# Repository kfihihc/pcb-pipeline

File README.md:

# pcb-pipeline: skills, toolkit and merge gate for open-source PCB design

English | [中文](README.zh-CN.md)

A set of skills for Claude Code and Codex (Agent Skills format) plus pcbkit, a toolkit that is copied into each board project at a fixed version. Together they cover the whole KiCad 10 board flow:

requirements → parts → datasheet facts → official reference design comparison → schematic as code → simulation → rules, placement, routing → gate → review → release

```mermaid
flowchart LR
  classDef agent stroke:#3987e5,stroke-width:2px
  classDef human stroke:#d95926,stroke-width:2px
  classDef tool stroke:#199e70,stroke-width:2px
  S1(Requirements):::agent --> S2(Parts):::agent --> S3(Datasheets):::agent --> S4(Reference design):::agent --> S5(Schematic):::agent --> S6(Simulation):::agent --> S7(Layout):::agent
  S7 --> G{8-check gate}:::tool
  G -- fail --> S7
  G -- pass --> R{{Review}}:::human --> P(Release):::agent --> B{{Bring-up}}:::human
  B -- errata --> S1
```

The principles:

- KiCad is the single source of truth for the board.
- Design intent is kept as text.
- Every change passes a deterministic gate in Git and CI.
- Routing uses open routers.
- Agents change a design only through branches, change notes and pull requests.

> **Language.** The skill instructions and the project documents are written in Chinese. Every skill description includes an English sentence to help agents identify relevant tasks in English; automatic selection has not been systematically evaluated.

- How to use it: [docs/SKILLS.zh-CN.md](docs/SKILLS.zh-CN.md) (Chinese). It has an overview diagram, a quick reference for the ten skills, example prompts, the life cycle of one change, the evidence chain and the data flow.
- Why it is designed this way and what was verified: [PIPELINE.zh-CN.md](PIPELINE.zh-CN.md) (Chinese).
- The diagrams are Mermaid, which GitHub renders directly. For other viewers, SVG copies are in `docs/diagrams/`.

It grew out of an earlier survey of AI and EDA tools for hardware design (not part of this repository) and the experience of building a KiCad replica of an ESP32-S3 AMOLED board.

## Skills

| Skill | What it does | Bundled scripts |
| --- | --- | --- |
| `pcb-pipeline` | Orchestrator: stages, artifacts, rules for transactional changes; creates or adopts a project; upgrades pcbkit | `scripts/new_project.py`, `kit/`, `assets/template/` |
| `pcb-parts` | Offline search of the JLCPCB/LCSC parts library, alternates, BOM stock and cost, live prices | `scripts/jlc_parts.py` |
| `pcb-datasheet` | Datasheet download with provenance, per-page search and rendering, `facts.toml` with page references, pinout check against KiCad | `scripts/datasheet.py` |
| `pcb-refdesign` | Export of official reference designs (KiCad, Altium, EAGLE, PDF), chip-centred surroundings, pin-by-pin comparison | `scripts/refnet.py` |
| `pcb-schematic` | SKiDL circuit code → readable KiCad schematic; connectivity intent | (in the project: `pcbkit/sch_gen.py`) |
| `pcb-sim` | SPICE benches, corners and assertions (libngspice) | (in the project: `pcbkit/sim.py`) |
| `pcb-layout` | Board outline, rules, net classes, pours, keepouts; sync, placement, pre-routing; transactional routing with KiCadRoutingTools | `scripts/setup_krt.sh` |
| `pcb-gate` | The 8-check gate, declarative metrics, CI, revision diff and change-scope check | (in the project: `pcbkit/gate.py`, `metrics.py`, `board_diff.py`) |
| `pcb-review` | Review packet (KiCanvas, interactive BOM, PcbDraw drawings, EMC pre-check leads), reviewer plus devil's-advocate passes, findings turned into gate checks | `scripts/setup_kicad_happy.sh` (in the project: `pcbkit/review.py`) |
| `pcb-release` | Fabrication and review package, JLCPCB BOM/CPL, interactive BOM, panelization (the user decides), pre-order checks, tagging | (in the project: `pcbkit/release.py`, `extras.py`) |

The gate runs these 8 checks:

1. ERC.
2. DRC with schematic parity.
3. A rules canary: a broken `.kicad_dru` is otherwise dropped silently.
4. Zone refill.
5. Netlist checks: connectivity intent, pins against pads, BOM fields and the parts register.
6. Board metrics.
7. Simulation assertions.
8. Reproduction of generated files.

## Installing the skills

### 1. Prerequisites

| Needed for | Requirement |
| --- | --- |
| Everything | Linux with KiCad 10 from your distribution: `kicad-cli` and KiCad's `pcbnew` Python module. Tested with Debian's KiCad 10.0.6 and Python 3.14. pcbkit uses the system KiCad and never downloads its own copy |
| Datasheets | poppler-utils (`pdftotext`, `pdfinfo`, `pdftoppm`) |
| Simulation | libngspice (Debian: `libngspice0`, already pulled in by KiCad) |
| Board projects | [uv](https://docs.astral.sh/uv/) for the Python dependency groups (SKiDL, router, optional outputs), and git |
| Tests only | rsync |
| The agent | [Claude Code](https://claude.com/claude-code) and/or Codex |

On Debian or Ubuntu:

```bash
sudo apt install kicad poppler-utils libngspice0 git rsync pipx
pipx install uv          # or the installer from the uv website
```

### 2. Get the repository

```bash
git clone https://github.com/kfihihc/pcb-pipeline.git
cd pcb-pipeline
```

Keep the clone: the skills are installed as symbolic links into it.

### 3. Link the skills

`install.sh` links every folder under `skills/` into the personal skill folders of Claude Code (`~/.claude/skills/`) and Codex (`~/.codex/skills/`). It links only into folders that already exist, so create the ones for the agents you use first:

```bash
mkdir -p ~/.claude/skills     # Claude Code
mkdir -p ~/.codex/skills      # Codex, only if you use it
./install.sh
```

Expected output, once per skill and agent:

```
linked  /home/you/.claude/skills/pcb-pipeline
linked  /home/you/.claude/skills/pcb-parts
...
```

- `skip … (not present)` means that agent's skill folder does not exist; create it and run `./install.sh` again.
- `CONFLICT … exists and is not a link` means a skill of the same name is already installed. The script leaves it untouched; move it away first if you want this one.

Install all ten skills. They refer to each other: the orchestrator hands work to the stage skills, and the release skill uses references from the layout skill.

### 4. Check the installation

```bash
./install.sh --check
```

This lists every link (`ok`, `missing` or `CONFLICT`) and checks the dependencies: `kicad-cli`, poppler, uv, git, libngspice, the parts database, the router and kicad-happy.

Then start a **new** Claude Code session so it loads the skills, and try one of these:

- type `/pcb-pipeline`;
- or just describe the task, for example "Design a small USB-C to 3.3 V board with pcb-pipeline". The agent chooses the skill from its description.

The ten skills have been discovered in both Claude Code and Codex, and their instructions have been read in Codex. This verifies discovery and access, not an end-to-end board design run in both agents.

### 5. One-time downloads (when a stage first needs them)

All of these go to `~/.cache/pcb-pipeline/`, outside the repository:

| For | Command | Notes |
| --- | --- | --- |
| Parts search (`pcb-parts`) | `python3 skills/pcb-parts/scripts/jlc_parts.py fetch --db current` | JLCPCB parts database, about 180 MB |
| Autorouting (`pcb-layout`) | `skills/pcb-layout/scripts/setup_krt.sh` | KiCadRoutingTools v0.22.1 with its own uv environment |
| EMC pre-check (`pcb-review`, optional) | `skills/pcb-review/scripts/setup_kicad_happy.sh` | kicad-happy v2.3.1; only its analysis scripts are used, its skills are not installed |

The optional outputs (KiKit panel, InteractiveHtmlBom, PcbDraw) are installed per board project, in that project's uv environment: run `uv sync --group extras` in the project. `kicanvas.js` ships with pcbkit. [docs/external-tools.zh-CN.md](docs/external-tools.zh-CN.md) (Chinese) explains how these tools were chosen and why KiBot is not used.

### Updating and removing

- **Update the skills:** `git pull` in the clone. The links pick up the change at once; start a new agent session.
- **Update a board project's toolkit:** each project keeps its own copy of pcbkit, so upgrade it deliberately, on its own branch, then run the gate:

  ```bash
  python3 <clone>/skills/pcb-pipeline/scripts/new_project.py <board> --update-kit
  ```
- **Remove:** `./install.sh --uninstall` removes only the links that point into this clone.

### Other ways to install

- **One project only (Claude Code):** link the skill folders into that project's `.claude/skills/` instead of `~/.claude/skills/`.
- **Copy instead of link:** copying `skills/*` also works, but then `git pull` no longer updates them.

## Quick start

```bash
P=$PWD/skills       # run inside the pcb-pipeline clone
python3 "$P/pcb-pipeline/scripts/new_project.py" ~/boards/my-board --name my-board --title "My board" --size 40x30
cd ~/boards/my-board && git init
# then tell Claude Code / Codex: "Design this board with pcb-pipeline. The requirements are ..."
python3 pcbkit/gate.py          # the gate; run it at any time
```

To adopt an existing KiCad project:

```bash
# Run from the pcb-pipeline clone; replace /path/to/existing-board.
python3 skills/pcb-pipeline/scripts/new_project.py /path/to/existing-board \
  --adopt --pcb x.kicad_pcb --sch x.kicad_sch
```

See `examples/s3-adoption/` for a worked case.

## Examples

- [examples/usb-ldo/](examples/usb-ldo/): a small two-layer board taken from nothing to a fabrication package. Its README lists the problems each stage actually caught.
- [examples/s3-adoption/](examples/s3-adoption/): the gate applied to the S3 AMOLED replica, with its 30 existing thresholds rewritten as declarative metrics.

## Tests

```bash
tests/run_tests.sh        # about 2 minutes
```

The suite runs the example's gate and negative tests for each check. It also covers simulation, reference designs, parts search, datasheets, and the optional outputs including panelization. A test whose data or tool is missing is skipped, not failed.

## License

MIT, see [LICENSE](LICENSE). This covers the skills, pcbkit, the documentation and the example designs.

New board projects default to MIT; use `new_project.py --license <identifier>` to choose another license. Check the upstream license when adopting or deriving an existing design.

Exceptions:

- **KiCanvas:** `kicanvas.js` (`skills/pcb-pipeline/kit/vendor/` and its copy in the example) keeps its own MIT license and copyright, in `kicanvas.LICENSE.md` next to it.
- **KiCad libraries:** symbols and footprints from the KiCad libraries used in the example boards are under the KiCad library license (CC-BY-SA 4.0 with an exception for designs that use them).
- **Tools fetched at setup:** these keep their own licenses. All are MIT: KiCadRoutingTools, kicad-happy, KiKit, InteractiveHtmlBom and PcbDraw.

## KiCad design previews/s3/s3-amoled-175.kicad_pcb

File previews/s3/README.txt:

Open in a browser over HTTP (file:// does not work):
  python3 -m http.server --directory s3 8000
  then http://localhost:8000/   (any free port; Ctrl+C stops the server)

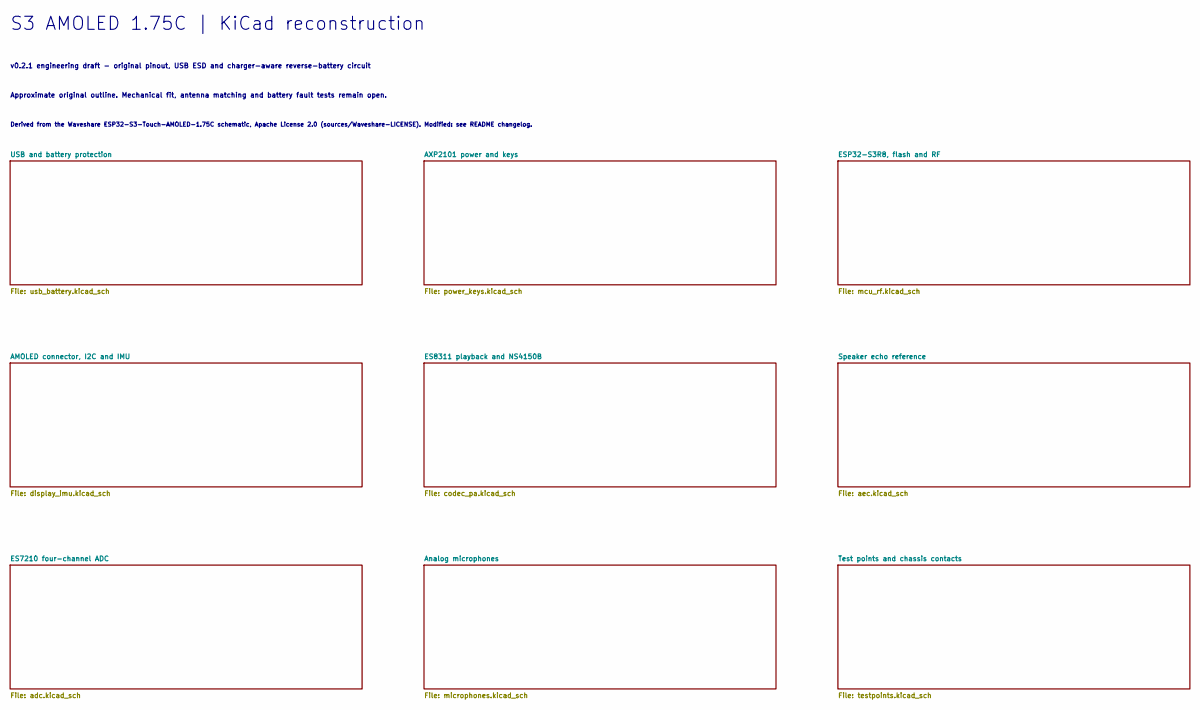
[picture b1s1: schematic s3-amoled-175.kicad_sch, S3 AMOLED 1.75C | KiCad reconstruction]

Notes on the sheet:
Approximate original outline. Mechanical fit, antenna matching and battery fault tests remain open.
v0.2.1 engineering draft - original pinout, USB ESD and charger-aware reverse-battery circuit
S3 AMOLED 1.75C | KiCad reconstruction
Derived from the Waveshare ESP32-S3-Touch-AMOLED-1.75C schematic, Apache License 2.0 (sources/Waveshare-LICENSE). Modified: see README changelog.

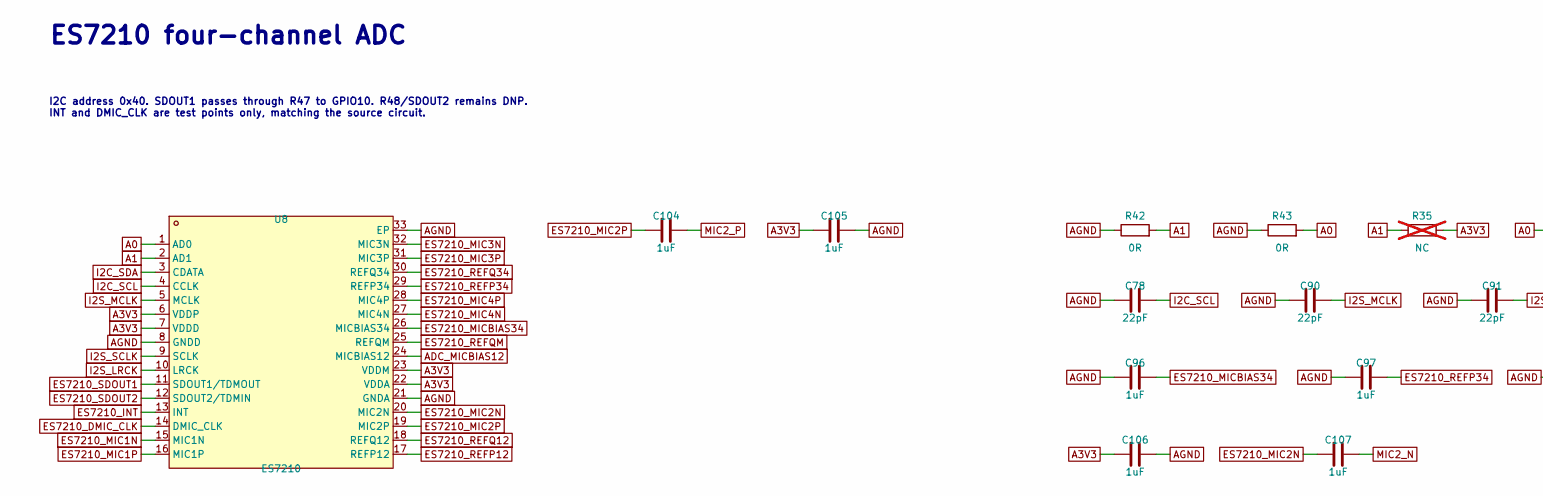
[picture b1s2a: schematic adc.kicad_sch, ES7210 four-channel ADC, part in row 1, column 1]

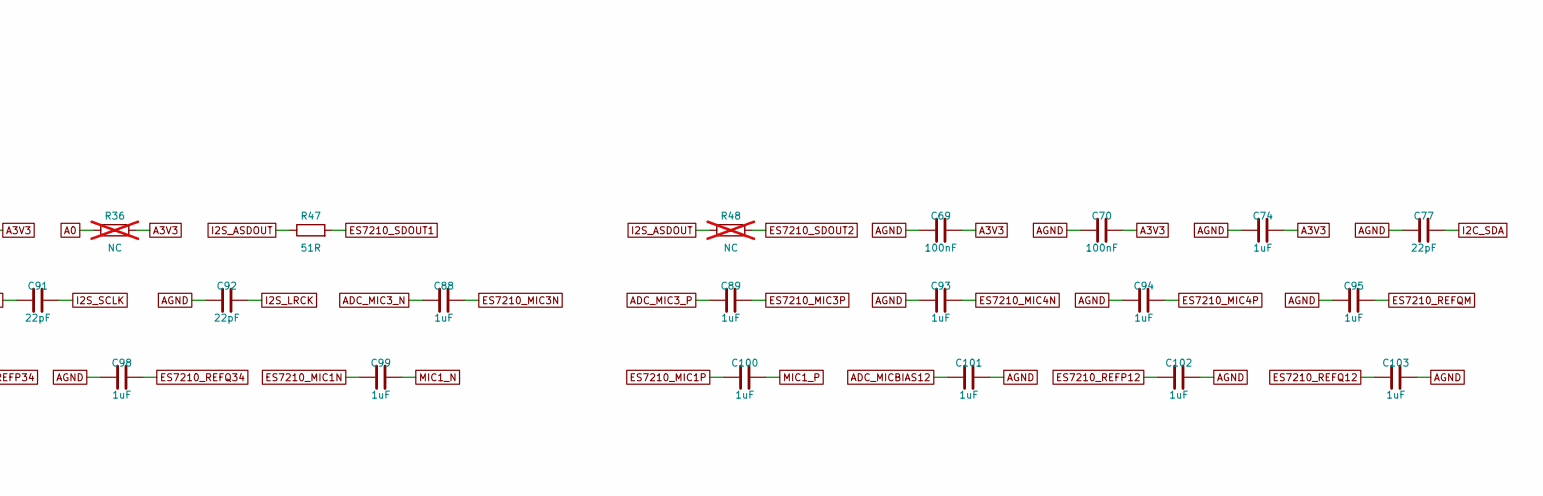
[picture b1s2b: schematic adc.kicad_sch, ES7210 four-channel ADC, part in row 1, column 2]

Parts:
C69, C70: 100nF; C_0201_0603Metric_Tight; LCSC C190183
C74, C88, C89, C93, C94, C95, C96, C97, C98, C99, C100, C101, C102, C103, C104, C105, C106, C107: 1uF; C_0201_0603Metric_Tight; LCSC C76929
C77, C78, C90, C91, C92: 22pF; C_0201_0603Metric_Tight; LCSC C272881
R35, R36: NC; R_0402_1005Metric_Tight; not fitted
R42, R43: 0R; R_0402_1005Metric_Tight; LCSC C17168
R47: 51R; R_0201_0603Metric_Tight; LCSC C163499
R48: NC; R_0201_0603Metric_Tight; not fitted
U8: ES7210; QFN-32_L4.0-W4.0-P0.40-BL-EP2.7; MPN ES7210; LCSC C365743

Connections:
A0: R36.1, R43.2, U8.1 (AD0)
A1: R35.1, R42.2, U8.2 (AD1)
A3V3: C69.2, C70.2, C74.2, C105.1, C106.1, R35.2, R36.2, U8.6 (VDDP), U8.7 (VDDD), U8.22 (VDDA), U8.23 (VDDM); also elsewhere on the board
ADC_MIC3_N: C88.1; also elsewhere on the board
ADC_MIC3_P: C89.1; also elsewhere on the board
ADC_MICBIAS12: C101.1, U8.24 (MICBIAS12); also elsewhere on the board
AGND: C69.1, C70.1, C74.1, C77.1, C78.1, C90.1, C91.1, C92.1, C93.1, C94.1, C95.1, C96.1, C97.1, C98.1, C101.2, C102.2, C103.2, C105.2, C106.2, R42.1, R43.1, U8.8 (GNDD), U8.21 (GNDA), U8.33 (EP); also elsewhere on the board
ES7210_DMIC_CLK: U8.14 (DMIC_CLK); also elsewhere on the board
ES7210_INT: U8.13 (INT); also elsewhere on the board
ES7210_MIC1N: C99.1, U8.15 (MIC1N)
ES7210_MIC1P: C100.1, U8.16 (MIC1P)
ES7210_MIC2N: C107.1, U8.20 (MIC2N)
ES7210_MIC2P: C104.1, U8.19 (MIC2P)
ES7210_MIC3N: C88.2, U8.32 (MIC3N)
ES7210_MIC3P: C89.2, U8.31 (MIC3P)
ES7210_MIC4N: C93.2, U8.27 (MIC4N)
ES7210_MIC4P: C94.2, U8.28 (MIC4P)
ES7210_MICBIAS34: C96.2, U8.26 (MICBIAS34)
ES7210_REFP12: C102.1, U8.17 (REFP12)
ES7210_REFP34: C97.2, U8.29 (REFP34)
ES7210_REFQ12: C103.1, U8.18 (REFQ12)
ES7210_REFQ34: C98.2, U8.30 (REFQ34)
ES7210_REFQM: C95.2, U8.25 (REFQM)
ES7210_SDOUT1: R47.2, U8.11 (SDOUT1/TDMOUT)
ES7210_SDOUT2: R48.2, U8.12 (SDOUT2/TDMIN)
I2C_SCL: C78.2, U8.4 (CCLK); also elsewhere on the board
I2C_SDA: C77.2, U8.3 (CDATA); also elsewhere on the board
I2S_ASDOUT: R47.1, R48.1; also elsewhere on the board
I2S_LRCK: C92.2, U8.10 (LRCK); also elsewhere on the board
I2S_MCLK: C90.2, U8.5 (MCLK); also elsewhere on the board
I2S_SCLK: C91.2, U8.9 (SCLK); also elsewhere on the board
MIC1_N: C99.2; also elsewhere on the board
MIC1_P: C100.2; also elsewhere on the board
MIC2_N: C107.2; also elsewhere on the board
MIC2_P: C104.2; also elsewhere on the board

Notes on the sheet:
ES7210 four-channel ADC
I2C address 0x40. SDOUT1 passes through R47 to GPIO10. R48/SDOUT2 remains DNP. INT and DMIC_CLK are test points only, matching the source circuit.

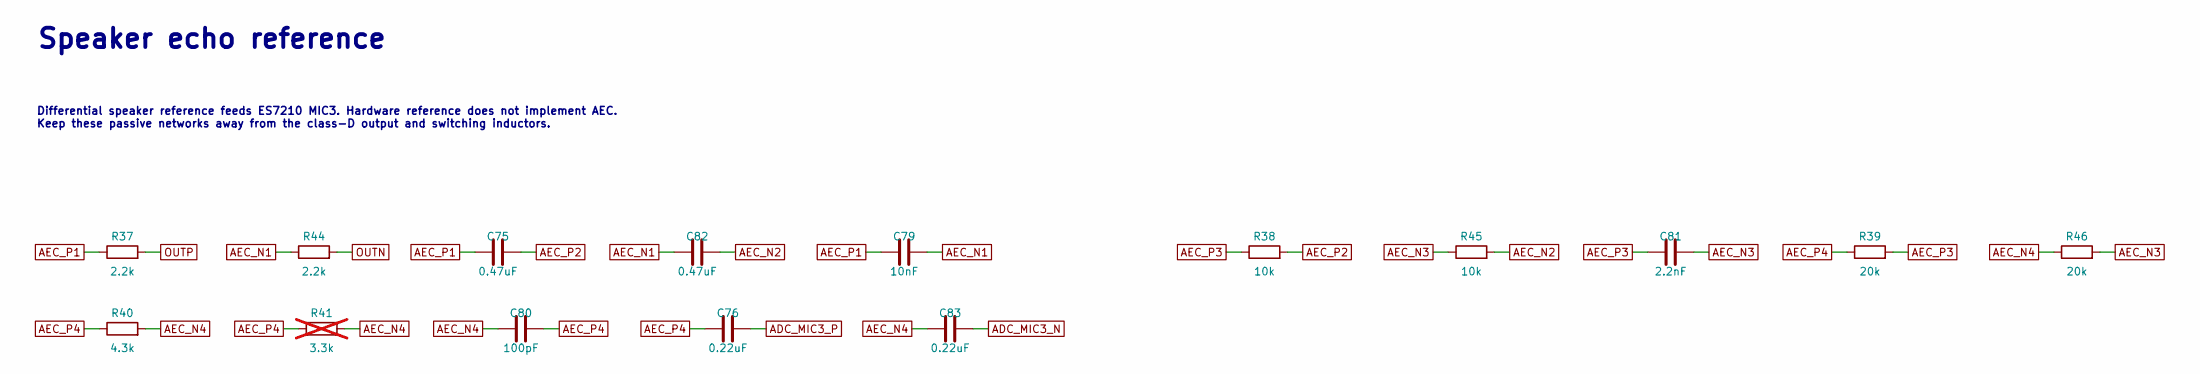
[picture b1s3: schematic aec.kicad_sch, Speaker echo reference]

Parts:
C75, C82: 0.47uF; C_0201_0603Metric_Tight; LCSC C88915
C76, C83: 0.22uF; C_0201_0603Metric_Tight; LCSC C76932
C79: 10nF; C_0201_0603Metric_Tight; LCSC C285010
C80: 100pF; C_0201_0603Metric_Tight; LCSC C272870
C81: 2.2nF; C_0201_0603Metric_Tight; LCSC C80433
R37, R44: 2.2k; R_0201_0603Metric_Tight; LCSC C142018
R38, R45: 10k; R_0201_0603Metric_Tight; LCSC C473048
R39, R46: 20k; R_0201_0603Metric_Tight; LCSC C295787
R40: 4.3k; R_0201_0603Metric_Tight; LCSC C423525
R41: 3.3k; R_0201_0603Metric_Tight; not fitted

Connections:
ADC_MIC3_N: C83.2; also elsewhere on the board
ADC_MIC3_P: C76.2; also elsewhere on the board
AEC_N1: C79.2, C82.1, R44.1
AEC_N2: C82.2, R45.2
AEC_N3: C81.2, R45.1, R46.2
AEC_N4: C80.1, C83.1, R40.2, R41.2, R46.1
AEC_P1: C75.1, C79.1, R37.1
AEC_P2: C75.2, R38.2
AEC_P3: C81.1, R38.1, R39.2
AEC_P4: C76.1, C80.2, R39.1, R40.1, R41.1
OUTN: R44.2; also elsewhere on the board
OUTP: R37.2; also elsewhere on the board

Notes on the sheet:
Speaker echo reference
Differential speaker reference feeds ES7210 MIC3. Hardware reference does not implement AEC. Keep these passive networks away from the class-D output and switching inductors.

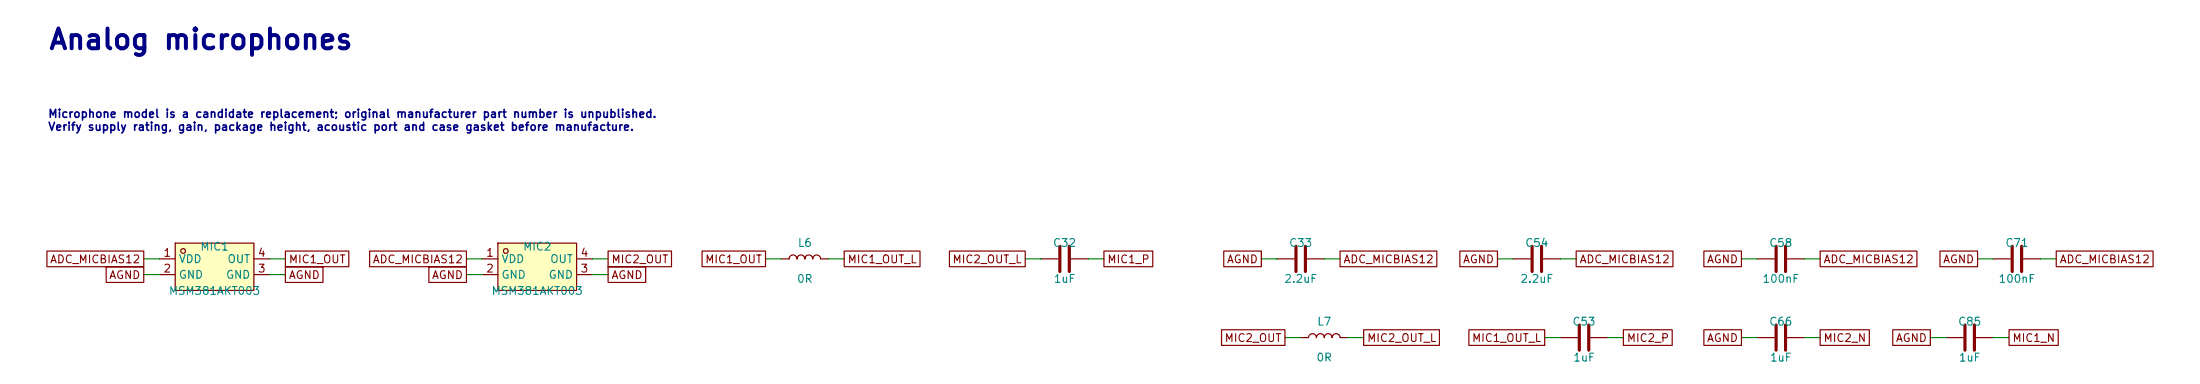
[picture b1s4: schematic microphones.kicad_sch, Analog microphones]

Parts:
C32, C53, C66, C85: 1uF; C_0201_0603Metric_Tight; LCSC C76929
C33, C54: 2.2uF; C_0201_0603Metric_Tight; LCSC C386031
C58, C71: 100nF; C_0201_0603Metric_Tight; LCSC C190183
L6, L7: 0R; R_0201_0603Metric_Tight; LCSC C106227
MIC1, MIC2: MSM381AKT003; MIC_MSM381AKT003_Tight; MPN MSM381AKT003; LCSC C51928211

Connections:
ADC_MICBIAS12: C33.2, C54.2, C58.2, C71.2, MIC1.1 (VDD), MIC2.1 (VDD); also elsewhere on the board
AGND: C33.1, C54.1, C58.1, C66.1, C71.1, C85.1, MIC1.2 (GND), MIC1.3 (GND), MIC2.2 (GND), MIC2.3 (GND); also elsewhere on the board
MIC1_N: C85.2; also elsewhere on the board
MIC1_OUT: L6.1, MIC1.4 (OUT)
MIC1_OUT_L: C53.1, L6.2
MIC1_P: C32.2; also elsewhere on the board
MIC2_N: C66.2; also elsewhere on the board
MIC2_OUT: L7.1, MIC2.4 (OUT)
MIC2_OUT_L: C32.1, L7.2
MIC2_P: C53.2; also elsewhere on the board

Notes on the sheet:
Microphone model is a candidate replacement; original manufacturer part number is unpublished. Verify supply rating, gain, package height, acoustic port and case gasket before manufacture.
Analog microphones

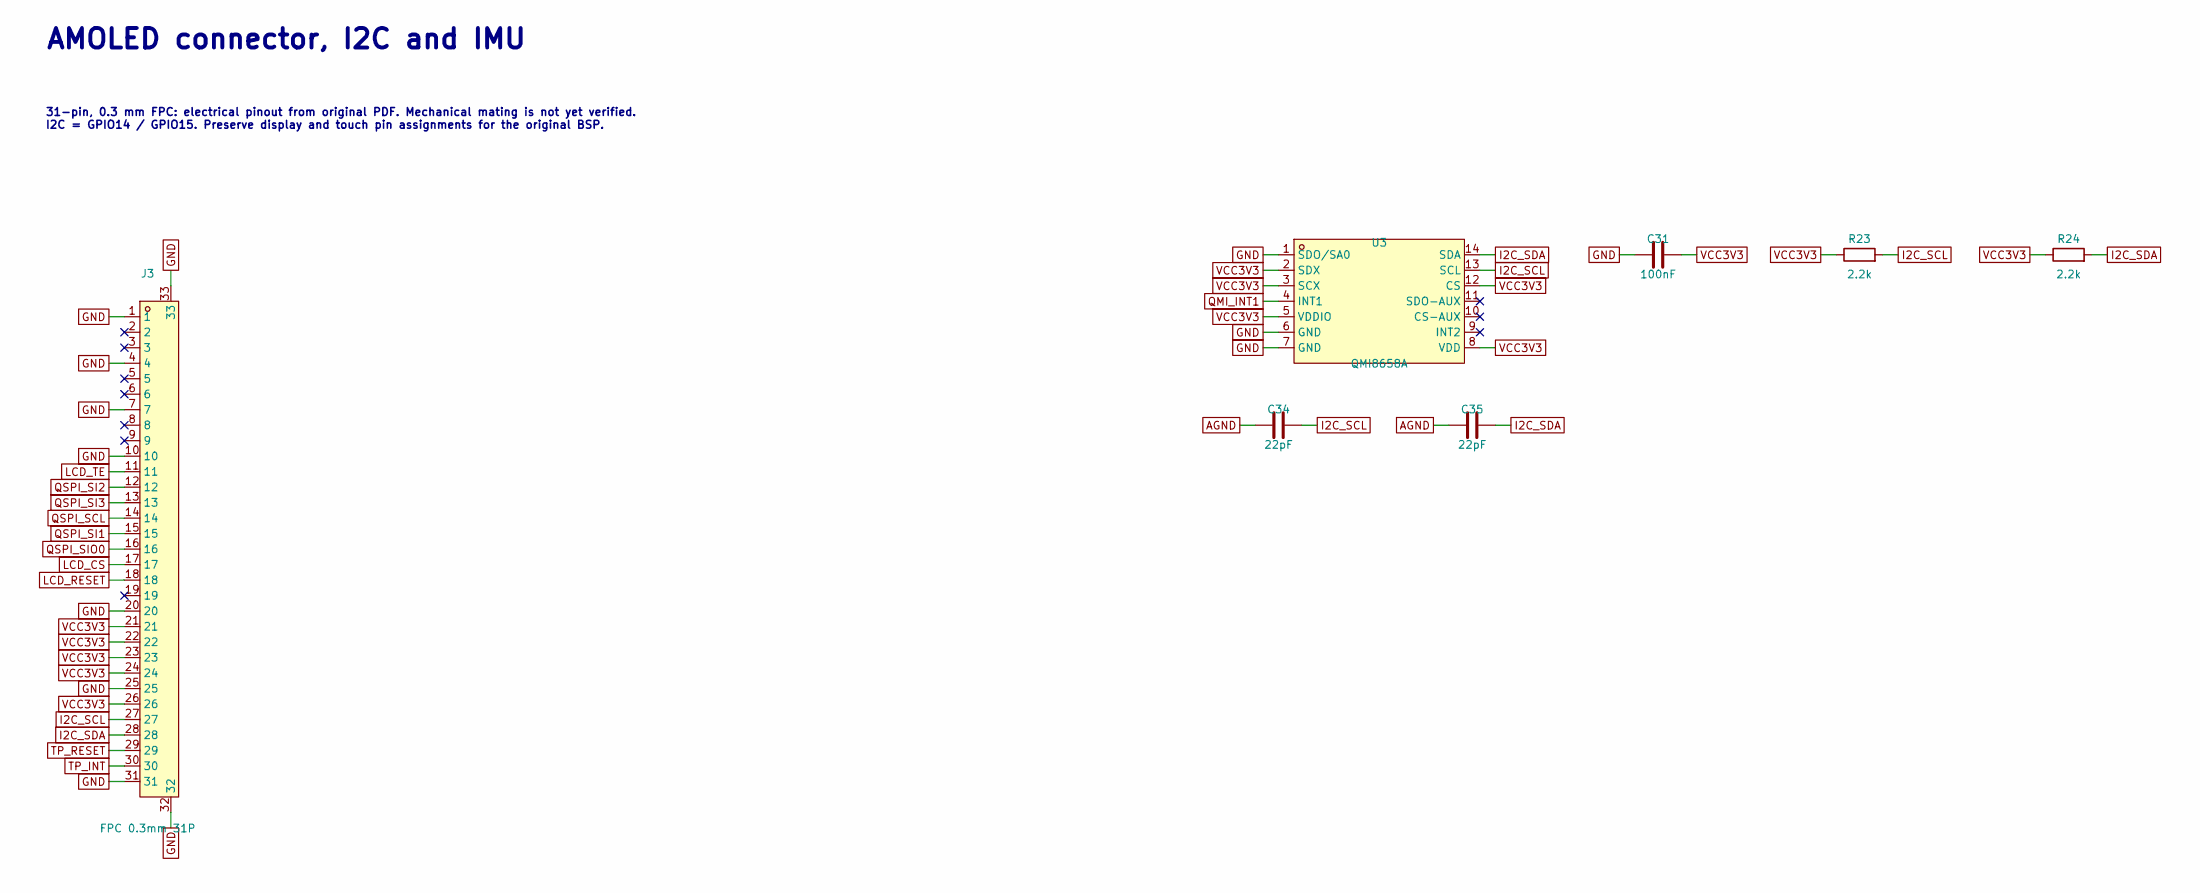
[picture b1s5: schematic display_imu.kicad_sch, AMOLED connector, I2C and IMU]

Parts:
C31: 100nF; C_0201_0603Metric_Tight; LCSC C190183
C34, C35: 22pF; C_0201_0603Metric_Tight; LCSC C272881
J3: FPC 0.3mm 31P; FPC-SMD_HC-FPC-0.3-31P-FHH10; MPN HC-FPC-0.3-31P-FHH10; LCSC C49166947
R23, R24: 2.2k; R_0201_0603Metric_Tight; LCSC C142018
U3: QMI8658A; LGA-14_L3.0-W2.5-P0.50-TL; MPN QMI8658A; LCSC C3021082

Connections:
AGND: C34.1, C35.1; also elsewhere on the board
GND: C31.1, J3.1, J3.4, J3.7, J3.10, J3.20, J3.25, J3.31, J3.32, J3.33, U3.1 (SDO/SA0), U3.6 (GND), U3.7 (GND); also elsewhere on the board
I2C_SCL: C34.2, J3.27, R23.2, U3.13 (SCL); also elsewhere on the board
I2C_SDA: C35.2, J3.28, R24.2, U3.14 (SDA); also elsewhere on the board
LCD_CS: J3.17; also elsewhere on the board
LCD_RESET: J3.18; also elsewhere on the board
LCD_TE: J3.11; also elsewhere on the board
QMI_INT1: U3.4 (INT1); also elsewhere on the board
QSPI_SCL: J3.14; also elsewhere on the board
QSPI_SI1: J3.15; also elsewhere on the board
QSPI_SI2: J3.12; also elsewhere on the board
QSPI_SI3: J3.13; also elsewhere on the board
QSPI_SIO0: J3.16; also elsewhere on the board
TP_INT: J3.30; also elsewhere on the board
TP_RESET: J3.29; also elsewhere on the board
VCC3V3: C31.2, J3.21, J3.22, J3.23, J3.24, J3.26, R23.1, R24.1, U3.2 (SDX), U3.3 (SCX), U3.5 (VDDIO), U3.8 (VDD), U3.12 (CS); also elsewhere on the board

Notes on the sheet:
31-pin, 0.3 mm FPC: electrical pinout from original PDF. Mechanical mating is not yet verified. I2C = GPIO14 / GPIO15. Preserve display and touch pin assignments for the original BSP.
AMOLED connector, I2C and IMU

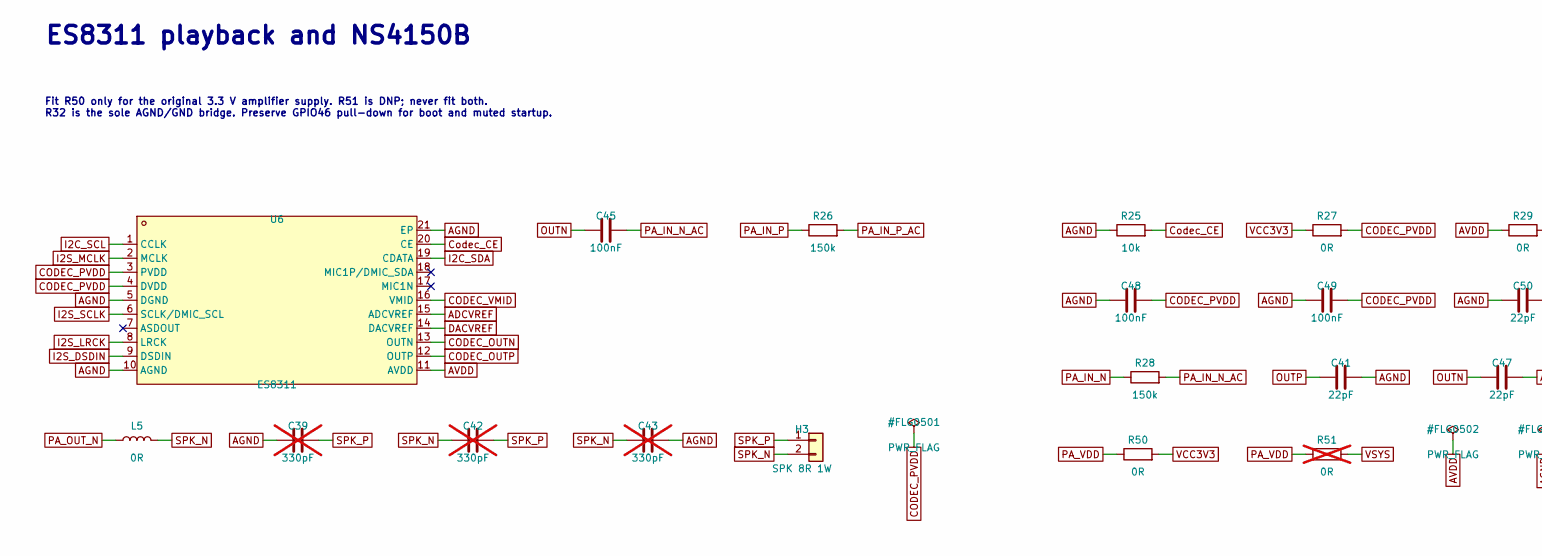
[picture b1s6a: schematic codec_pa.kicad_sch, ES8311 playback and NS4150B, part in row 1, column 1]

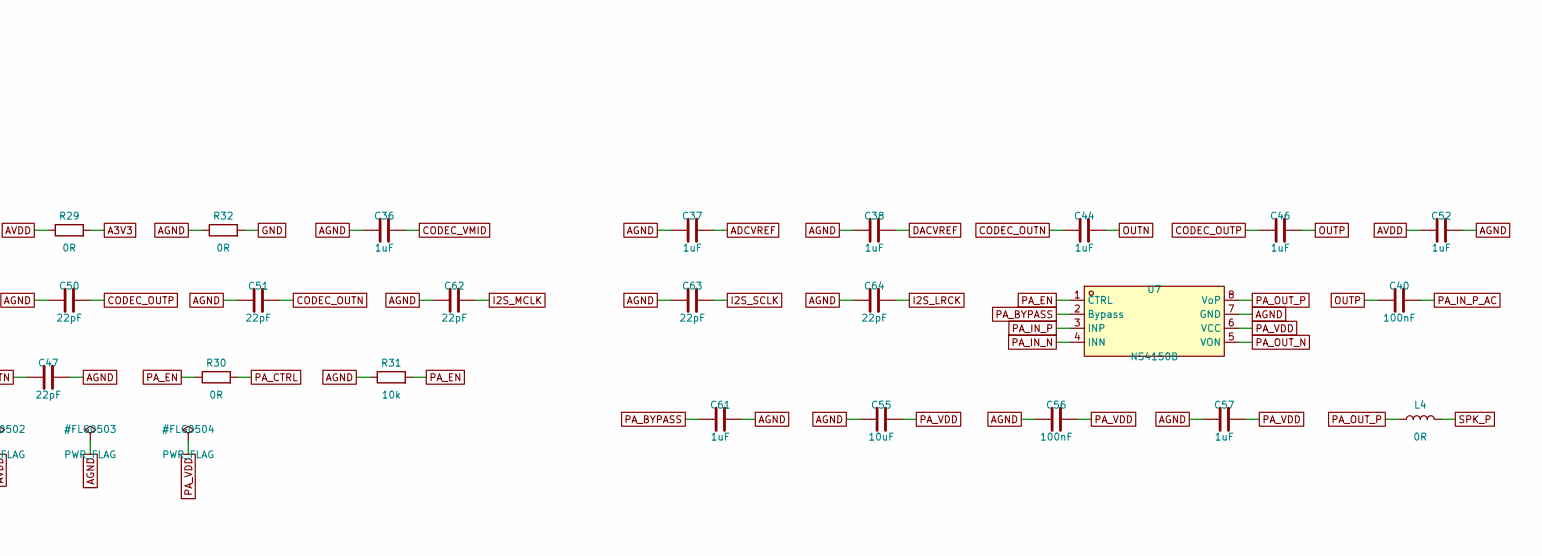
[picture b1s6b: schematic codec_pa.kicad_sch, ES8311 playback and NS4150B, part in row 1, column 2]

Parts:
C36, C37, C38, C44, C46, C52, C57, C61: 1uF; C_0201_0603Metric_Tight; LCSC C76929
C39, C42, C43: 330pF; C_0402_1005Metric_Tight; not fitted
C40, C45, C48, C49, C56: 100nF; C_0201_0603Metric_Tight; LCSC C190183
C41, C47, C50, C51, C62, C63, C64: 22pF; C_0201_0603Metric_Tight; LCSC C272881
C55: 10uF; C_0402_1005Metric_Tight; LCSC C15525
H3: SPK 8R 1W; SPK_Pads_2P; MPN 1511 腔体喇叭 8Ω 1W 线长30mm
L4, L5: 0R; R_0402_1005Metric_Tight; LCSC C17168
R25, R31: 10k; R_0201_0603Metric_Tight; LCSC C473048
R26, R28: 150k; R_0201_0603Metric_Tight; LCSC C274346
R27, R29, R30, R32, R50: 0R; R_0201_0603Metric_Tight; LCSC C106227
R51: 0R; R_0201_0603Metric_Tight; not fitted
U6: ES8311; WQFN-20_L3.0-W3.0-P0.40-BL-EP1.7; MPN ES8311; LCSC C962342
U7: NS4150B; MSOP-8_L3.0-W3.0-P0.65-LS5.0-BL; MPN NS4150B; LCSC C189961

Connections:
A3V3: R29.2; also elsewhere on the board
ADCVREF: C37.2, U6.15 (ADCVREF)
AGND: C36.1, C37.1, C38.1, C39.1, C41.2, C43.2, C47.2, C48.1, C49.1, C50.1, C51.1, C52.2, C55.1, C56.1, C57.1, C61.2, C62.1, C63.1, C64.1, R25.1, R31.1, R32.1, U6.5 (DGND), U6.10 (AGND), U6.21 (EP), U7.7 (GND); also elsewhere on the board
AVDD: C52.1, R29.1, U6.11 (AVDD)
CODEC_OUTN: C44.1, C51.2, U6.13 (OUTN)
CODEC_OUTP: C46.1, C50.2, U6.12 (OUTP)
CODEC_PVDD: C48.2, C49.2, R27.2, U6.3 (PVDD), U6.4 (DVDD)
CODEC_VMID: C36.2, U6.16 (VMID)
Codec_CE: R25.2, U6.20 (CE)
DACVREF: C38.2, U6.14 (DACVREF)
GND: R32.2; also elsewhere on the board
I2C_SCL: U6.1 (CCLK); also elsewhere on the board
I2C_SDA: U6.19 (CDATA); also elsewhere on the board
I2S_DSDIN: U6.9 (DSDIN); also elsewhere on the board
I2S_LRCK: C64.2, U6.8 (LRCK); also elsewhere on the board
I2S_MCLK: C62.2, U6.2 (MCLK); also elsewhere on the board
I2S_SCLK: C63.2, U6.6 (SCLK/DMIC_SCL); also elsewhere on the board
OUTN: C44.2, C45.1, C47.1; also elsewhere on the board
OUTP: C40.1, C41.1, C46.2; also elsewhere on the board
PA_BYPASS: C61.1, U7.2 (Bypass)
PA_CTRL: R30.2; also elsewhere on the board
PA_EN: R30.1, R31.2, U7.1 (CTRL)
PA_IN_N: R28.1, U7.4 (INN)
PA_IN_N_AC: C45.2, R28.2
PA_IN_P: R26.1, U7.3 (INP)
PA_IN_P_AC: C40.2, R26.2
PA_OUT_N: L5.1, U7.5 (VON)
PA_OUT_P: L4.1, U7.8 (VoP)
PA_VDD: C55.2, C56.2, C57.2, R50.1, R51.1, U7.6 (VCC)
SPK_N: C42.1, C43.1, H3.2, L5.2
SPK_P: C39.2, C42.2, H3.1, L4.2
VCC3V3: R27.1, R50.2; also elsewhere on the board
VSYS: R51.2; also elsewhere on the board

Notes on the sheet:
Fit R50 only for the original 3.3 V amplifier supply. R51 is DNP; never fit both. R32 is the sole AGND/GND bridge. Preserve GPIO46 pull-down for boot and muted startup.
ES8311 playback and NS4150B

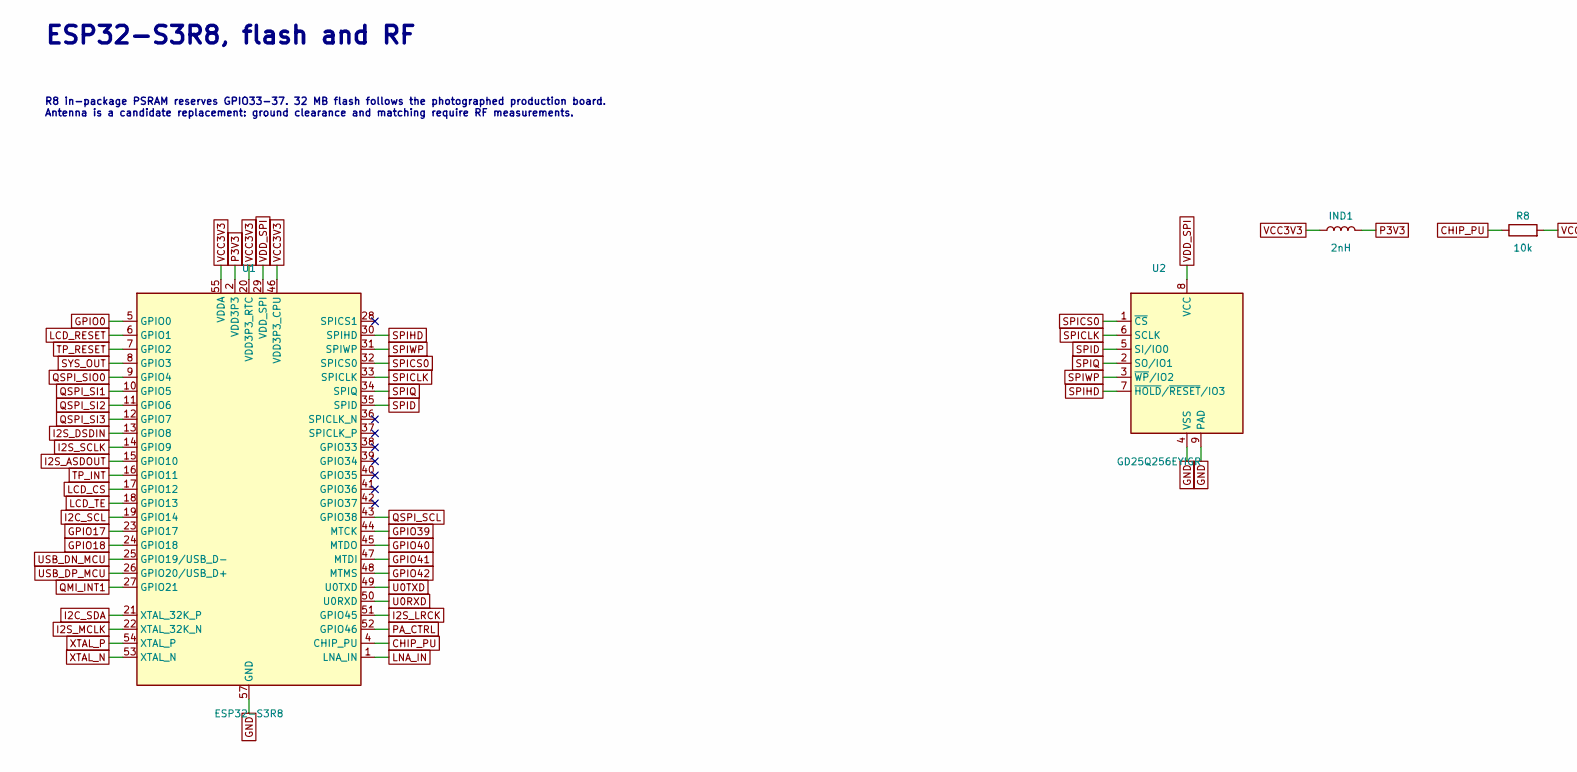
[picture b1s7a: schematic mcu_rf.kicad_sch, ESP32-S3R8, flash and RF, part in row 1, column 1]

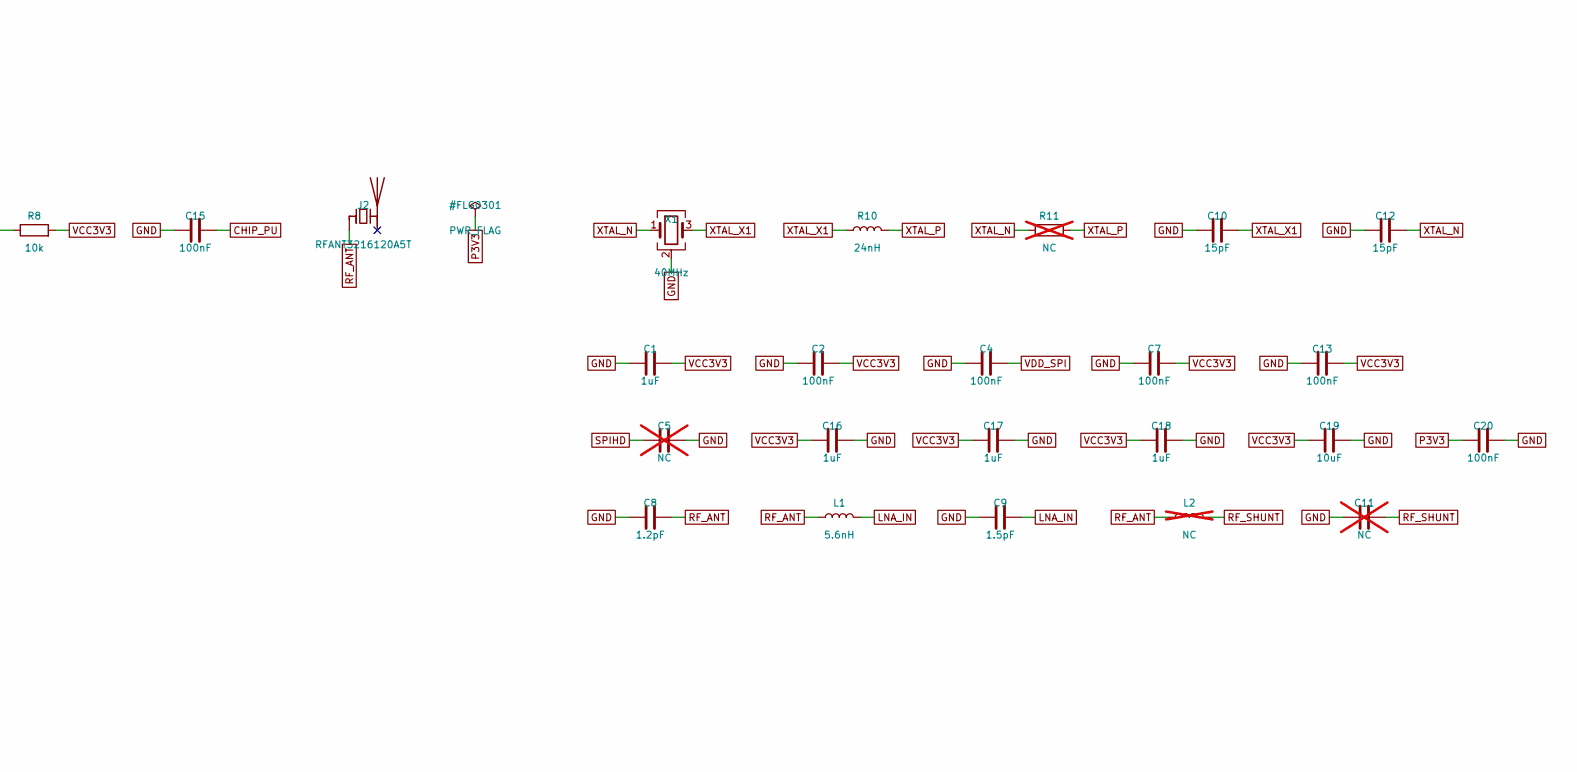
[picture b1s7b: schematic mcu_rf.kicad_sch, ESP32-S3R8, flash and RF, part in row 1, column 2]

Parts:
C1, C16, C17, C18: 1uF; C_0201_0603Metric_Tight; LCSC C76929
C2, C4, C7, C13, C15, C20: 100nF; C_0201_0603Metric_Tight; LCSC C190183
C5, C11: NC; C_0201_0603Metric_Tight; not fitted
C8: 1.2pF; C_0201_0603Metric_Tight; LCSC C326704
C9: 1.5pF; C_0201_0603Metric_Tight; LCSC C88913
C10, C12: 15pF; C_0201_0603Metric_Tight; LCSC C277480
C19: 10uF; C_0402_1005Metric_Tight; LCSC C15525
IND1: 2nH; L_0201_0603Metric_Tight; LCSC C86125
J2: RFANT3216120A5T; FILTER-SMD_1206-2P-L3.2-W1.6-L; MPN RFANT3216120A5T; LCSC C127629
L1: 5.6nH; L_0201_0603Metric_Tight; LCSC C2991782
L2: NC; L_0201_0603Metric_Tight; not fitted
R8: 10k; R_0201_0603Metric_Tight; LCSC C473048
R10: 24nH; L_0201_0603Metric_Tight; LCSC C2991767
R11: NC; R_0201_0603Metric_Tight; not fitted
U1: ESP32-S3R8; QFN-56-1EP_7x7mm_P0.4mm_EP4x4mm_ThermalVias; MPN ESP32-S3R8; LCSC C2913194
U2: GD25Q256EYIGR; WSON-8-1EP_8x6mm_P1.27mm_EP3.4x4.3mm; MPN GD25Q256EYIGR; LCSC C2927043
X1: 40MHz; Crystal_SMD_2520-4Pin_2.5x2.0mm; MPN X252040MMB4SI; LCSC C2885592

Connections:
CHIP_PU: C15.2, R8.1, U1.4 (CHIP_PU); also elsewhere on the board
GND: C1.1, C2.1, C4.1, C5.2, C7.1, C8.1, C9.1, C10.1, C11.1, C12.1, C13.1, C15.1, C16.2, C17.2, C18.2, C19.2, C20.2, U1.57 (GND), U2.4 (VSS), U2.9 (PAD), X1.2 (G), X1.4 (G); also elsewhere on the board
GPIO0: U1.5 (GPIO0); also elsewhere on the board
GPIO17: U1.23 (GPIO17); also elsewhere on the board
GPIO18: U1.24 (GPIO18); also elsewhere on the board
GPIO39: U1.44 (MTCK); also elsewhere on the board
GPIO40: U1.45 (MTDO); also elsewhere on the board
GPIO41: U1.47 (MTDI); also elsewhere on the board
GPIO42: U1.48 (MTMS); also elsewhere on the board
I2C_SCL: U1.19 (GPIO14); also elsewhere on the board
I2C_SDA: U1.21 (XTAL_32K_P); also elsewhere on the board
I2S_ASDOUT: U1.15 (GPIO10); also elsewhere on the board
I2S_DSDIN: U1.13 (GPIO8); also elsewhere on the board
I2S_LRCK: U1.51 (GPIO45); also elsewhere on the board
I2S_MCLK: U1.22 (XTAL_32K_N); also elsewhere on the board
I2S_SCLK: U1.14 (GPIO9); also elsewhere on the board
LCD_CS: U1.17 (GPIO12); also elsewhere on the board
LCD_RESET: U1.6 (GPIO1); also elsewhere on the board
LCD_TE: U1.18 (GPIO13); also elsewhere on the board
LNA_IN: C9.2, L1.2, U1.1 (LNA_IN)
P3V3: C20.1, IND1.2, U1.2 (VDD3P3), U1.3 (VDD3P3)
PA_CTRL: U1.52 (GPIO46); also elsewhere on the board
QMI_INT1: U1.27 (GPIO21); also elsewhere on the board
QSPI_SCL: U1.43 (GPIO38); also elsewhere on the board
QSPI_SI1: U1.10 (GPIO5); also elsewhere on the board
QSPI_SI2: U1.11 (GPIO6); also elsewhere on the board
QSPI_SI3: U1.12 (GPIO7); also elsewhere on the board
QSPI_SIO0: U1.9 (GPIO4); also elsewhere on the board
RF_ANT: C8.2, J2.1 (FEED), L1.1, L2.1
RF_SHUNT: C11.2, L2.2
SPICLK: U1.33 (SPICLK), U2.6 (SCLK)
SPICS0: U1.32 (SPICS0), U2.1 (~CS)
SPID: U1.35 (SPID), U2.5 (SI/IO0)
SPIHD: C5.1, U1.30 (SPIHD), U2.7 (~HOLD/~RESET/IO3)
SPIQ: U1.34 (SPIQ), U2.2 (SO/IO1)
SPIWP: U1.31 (SPIWP), U2.3 (~WP/IO2)
SYS_OUT: U1.8 (GPIO3); also elsewhere on the board
TP_INT: U1.16 (GPIO11); also elsewhere on the board
TP_RESET: U1.7 (GPIO2); also elsewhere on the board
U0RXD: U1.50 (U0RXD); also elsewhere on the board
U0TXD: U1.49 (U0TXD); also elsewhere on the board
USB_DN_MCU: U1.25 (GPIO19/USB_D-); also elsewhere on the board
USB_DP_MCU: U1.26 (GPIO20/USB_D+); also elsewhere on the board
VCC3V3: C1.2, C2.2, C7.2, C13.2, C16.1, C17.1, C18.1, C19.1, IND1.1, R8.2, U1.20 (VDD3P3_RTC), U1.46 (VDD3P3_CPU), U1.55 (VDDA), U1.56 (VDDA); also elsewhere on the board
VDD_SPI: C4.2, U1.29 (VDD_SPI), U2.8 (VCC)
XTAL_N: C12.2, R11.1, U1.53 (XTAL_N), X1.1
XTAL_P: R10.2, R11.2, U1.54 (XTAL_P)
XTAL_X1: C10.2, R10.1, X1.3

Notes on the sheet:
R8 in-package PSRAM reserves GPIO33-37. 32 MB flash follows the photographed production board. Antenna is a candidate replacement: ground clearance and matching require RF measurements.
ESP32-S3R8, flash and RF
